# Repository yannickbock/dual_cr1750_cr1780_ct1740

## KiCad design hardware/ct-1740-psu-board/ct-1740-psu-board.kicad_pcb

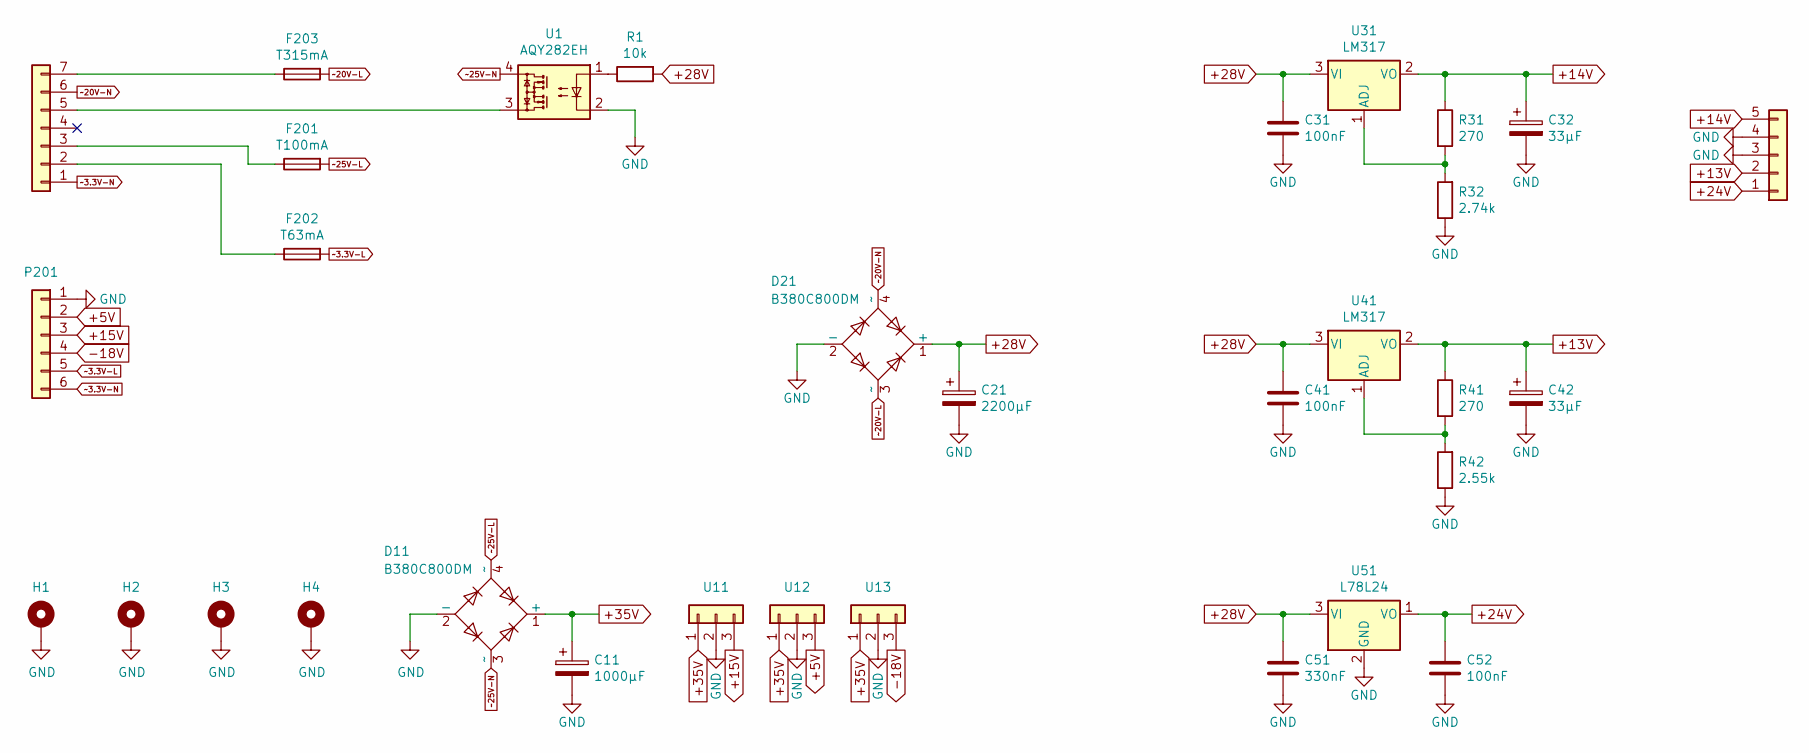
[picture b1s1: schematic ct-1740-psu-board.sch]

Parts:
C11: 1000µF; CP_Radial_D16.0mm_P7.50mm
C21: 2200µF; CP_Radial_D16.0mm_P7.50mm
C31, C41, C52: 100nF; C_Disc_D4.3mm_W1.9mm_P5.00mm
C32, C42: 33µF; CP_Radial_D5.0mm_P2.00mm
C51: 330nF; C_Disc_D4.3mm_W1.9mm_P5.00mm
D11, D21: B380C800DM; Diode_Bridge_DIP-4_W7.62mm_P5.08mm
F201: T100mA; Fuseholder5x20_horiz_open_inline_Type-I
F202: T63mA; Fuseholder5x20_horiz_open_inline_Type-I
F203: T315mA; Fuseholder5x20_horiz_open_inline_Type-I
H1, H2, H3, H4: MountingHole_Pad; MountingHole_4mm_Pad
J1: Conn_01x07
J3: Conn_01x05
P201: Conn_01x06
R1: 10k; R_Axial_DIN0207_L6.3mm_D2.5mm_P10.16mm_Horizontal
R31, R41: 270; R_Axial_DIN0207_L6.3mm_D2.5mm_P5.08mm_Vertical
R32: 2.74k; R_Axial_DIN0207_L6.3mm_D2.5mm_P5.08mm_Vertical
R42: 2.55k; R_Axial_DIN0207_L6.3mm_D2.5mm_P5.08mm_Vertical
U1: AQY282EH; DIP-4_W7.62mm
U11, U12, U13: Conn_01x03; TO-220-3_Vertical
U31, U41: LM317; TO-220-3_Vertical
U51: L78L24; TO-92_Inline_Wide

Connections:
+5V: P201.2, U12.3
+13V: C42.1, J3.2, R41.1, U41.2 (VO)
+14V: C32.1, J3.5, R31.1, U31.2 (VO)
+15V: P201.3, U11.3
+24V: C52.1, J3.1, U51.1 (VO)
+28V: C21.1, C31.1, C41.1, C51.1, D21.1 (+), R1.2, U31.3 (VI), U41.3 (VI), U51.3 (VI)
+35V: C11.1, D11.1 (+), U11.1, U12.1, U13.1
-18V: P201.4, U13.3
GND: C11.2, C21.2, C31.2, C32.2, C41.2, C42.2, C51.2, C52.2, D11.2 (-), D21.2 (-), H1.1, H2.1, H3.1, H4.1, J3.3, J3.4, P201.1, R32.1, R42.1, U1.2, U11.2, U12.2, U13.2, U51.2 (GND)
unnamed: F201.1, J1.3
unnamed: F202.1, J1.2
unnamed: F203.1, J1.7
unnamed: J1.5, U1.3
unnamed: R1.1, U1.1
unnamed: R31.2, R32.2, U31.1 (ADJ)
unnamed: R41.2, R42.2, U41.1 (ADJ)
~~3.3-L: F202.2, P201.5
~~3.3-N: J1.1, P201.6
~~20-L: D21.3 (~~), F203.2
~~20-N: D21.4 (~~), J1.6
~~25-L: D11.4 (~~), F201.2
~~25-N: D11.3 (~~), U1.4

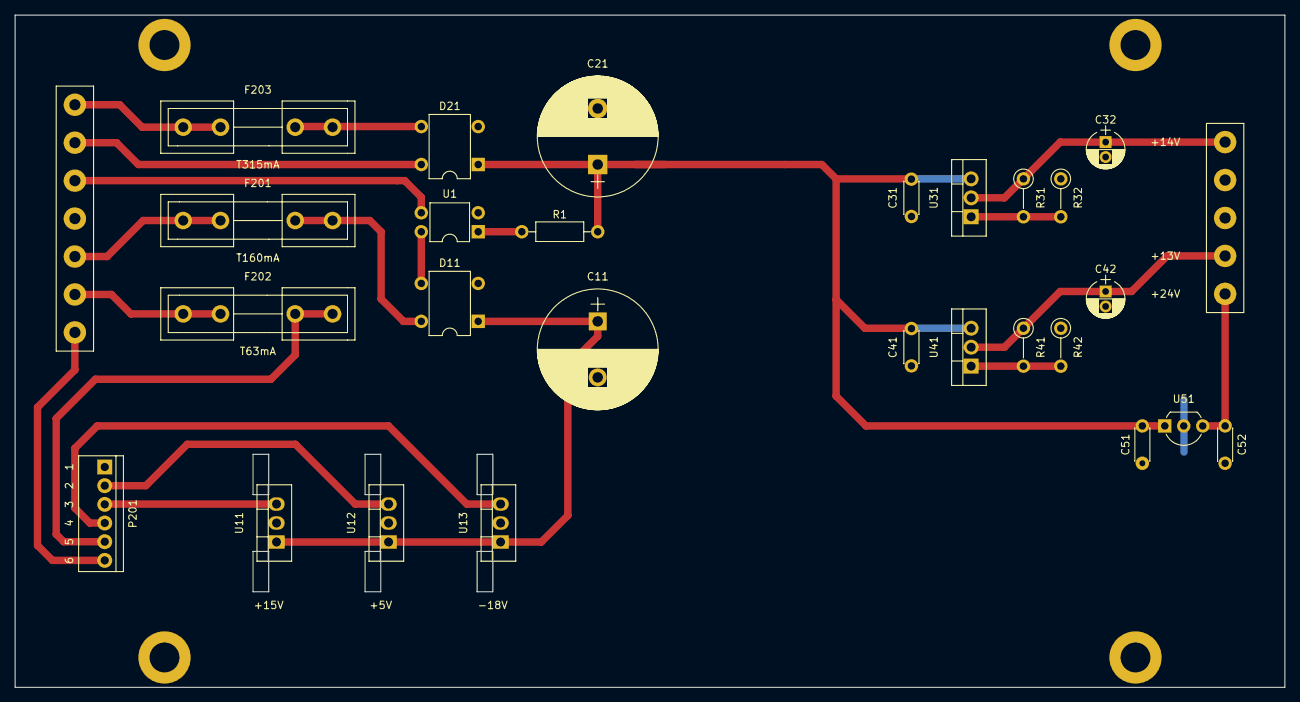
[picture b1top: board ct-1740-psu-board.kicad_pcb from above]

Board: 2 copper layers, 170.0 x 90.0 mm, 32 parts (0 on the bottom side), 22 nets.

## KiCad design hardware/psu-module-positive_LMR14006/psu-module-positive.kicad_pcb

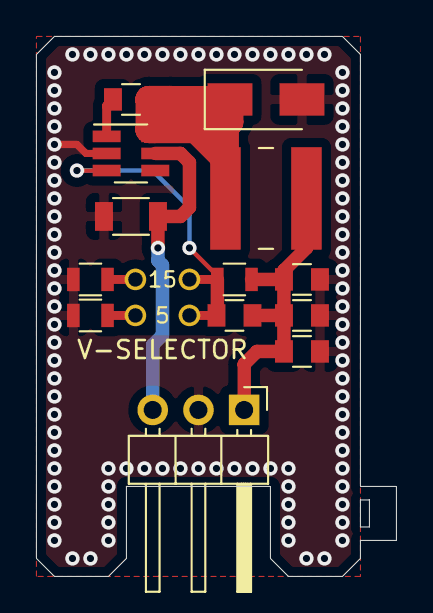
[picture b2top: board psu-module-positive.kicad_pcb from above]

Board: 2 copper layers, 20.0 x 30.0 mm, 15 parts (0 on the bottom side), 8 nets.

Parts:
C1: 10µF; C_1206
C2: 100nF; C_0805
C3, C4, C5, C6: 22µF; C_0805
D1: SS14; D_SMA
J5: Conn_01x03; Pin_Header_Angled_1x03_Pitch2.54mm
JP1: +15V; WireConnection_0.80mmDrill_ThinPad
JP2: +5V; WireConnection_0.80mmDrill_ThinPad
L1: 220µH; L_Wuerth_WE-PD2-Typ-MS
R1: 100k; R_0805
R2: 5.6k; R_0805
R3: 18k; R_0805
U1: BL9342; SOT-23-6_Handsoldering

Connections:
+5V|+15V: C3.1, C4.1, C5.1, C6.1, J5.1, L1.2, R1.1
+35V: C1.1, J5.3, U1.5
FB: C6.2, JP1.1, JP2.1, R1.2, U1.3
GND: C1.2, C3.2, C4.2, C5.2, D1.2, J5.2, R2.2, R3.2, U1.2
unnamed: C2.1, U1.1
unnamed: C2.2, D1.1, L1.1, U1.6
unnamed: JP1.2, R2.1
unnamed: JP2.2, R3.1
